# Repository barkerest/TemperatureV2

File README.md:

# TemperatureV2
A POE powered ethernet temperature sensor with two probes.

I wanted to be able to monitor temperatures in various locations
in my server rooms.  Most products on the market were designed
around having a head unit that you plug probes into.  This 
doesn't work for me since the locations I want to monitor have
a fair bit of distance between them.  My solution is a POE 
powered unit with two attached sensors.  I can put them anywhere
without concerning myself with power availability.

## Hardware
The system is based on an Adafruit Feather M0 Basic paired with
a Silicognition PoE FeatherWing and two DS18B20 sensors on leads.

The setup is extremely simple.  The FeatherWing gets attached 
to the M0, including the SDA and SCL pins.  A single 4.7k 
resistor ties pin 5 or 6 to 3v3 and the data lead of both sensors.

This setup costs about $50, and even spending that on each unit
I want to deploy, it still costs less than the commercial
solutions.

## Enclosure
To protect the unit we need an enclosure.  The enclosure needs
to be able to release about 1W of heat from the PoE components.

The enclosure included can easily accomplish that and exposes
the USB port for reprogramming (or external power).  The battery
connector is not exposed in this enclosure.

## Software
Based on some Arduino libraries, the included software manages
the sensors and serves up a very basic webpage.

You may notice this is V2.  V1 was considerably larger based 
on an Arduino.  It produced more heat, and the firmware had to
be altered for each unit to program the MAC address.  Since the
FeatherWing includes a globally unique MAC address, we don't 
need to change the firmware for each unit.

Since this is V2, I wanted to maintain backwards compatibility
with V1.  That's not hard, it just means that the root request
"/" can only return temperatures T1 and T2.  I added a second
endpoint "/v" which returns the MAC address (serial number) and
version of the software in addition to the temperatures.

In production, you'll want to setup DHCP reservations for the
sensors so that they are always where you expect.

## Bugs
None that I know of. However, you cannot power cycle the DS18B20
sensors rapidly.  Because of that, if the unit loses power for
less than a second it may not be able to locate one or both of
the sensors when it boots back up.  In production this shouldn't
happen, but I was able to produce the issue several times during
development by quickly unplugging and plugging back in to reset
the hardware.

## License
Copyright (C) 2021 Beau Barker

Permission is hereby granted, free of charge, to any person
obtaining a copy of this software and associated documentation
files (the "Software"), to deal in the Software without
restriction, including without limitation the rights to use,
copy, modify, merge, publish, distribute, sublicense, and/or
sell copies of the Software, and to permit persons to whom the
Software is furnished to do so, subject to the following
conditions:

The above copyright notice and this permission notice shall be
included in all copies or substantial portions of the Software.

THE SOFTWARE IS PROVIDED "AS IS", WITHOUT WARRANTY OF ANY KIND,
EXPRESS OR IMPLIED, INCLUDING BUT NOT LIMITED TO THE WARRANTIES
OF MERCHANTABILITY, FITNESS FOR A PARTICULAR PURPOSE AND
NONINFRINGEMENT. IN NO EVENT SHALL THE AUTHORS OR COPYRIGHT
HOLDERS BE LIABLE FOR ANY CLAIM, DAMAGES OR OTHER LIABILITY,
WHETHER IN AN ACTION OF CONTRACT, TORT OR OTHERWISE, ARISING
FROM, OUT OF OR IN CONNECTION WITH THE SOFTWARE OR THE USE OR
OTHER DEALINGS IN THE SOFTWARE.

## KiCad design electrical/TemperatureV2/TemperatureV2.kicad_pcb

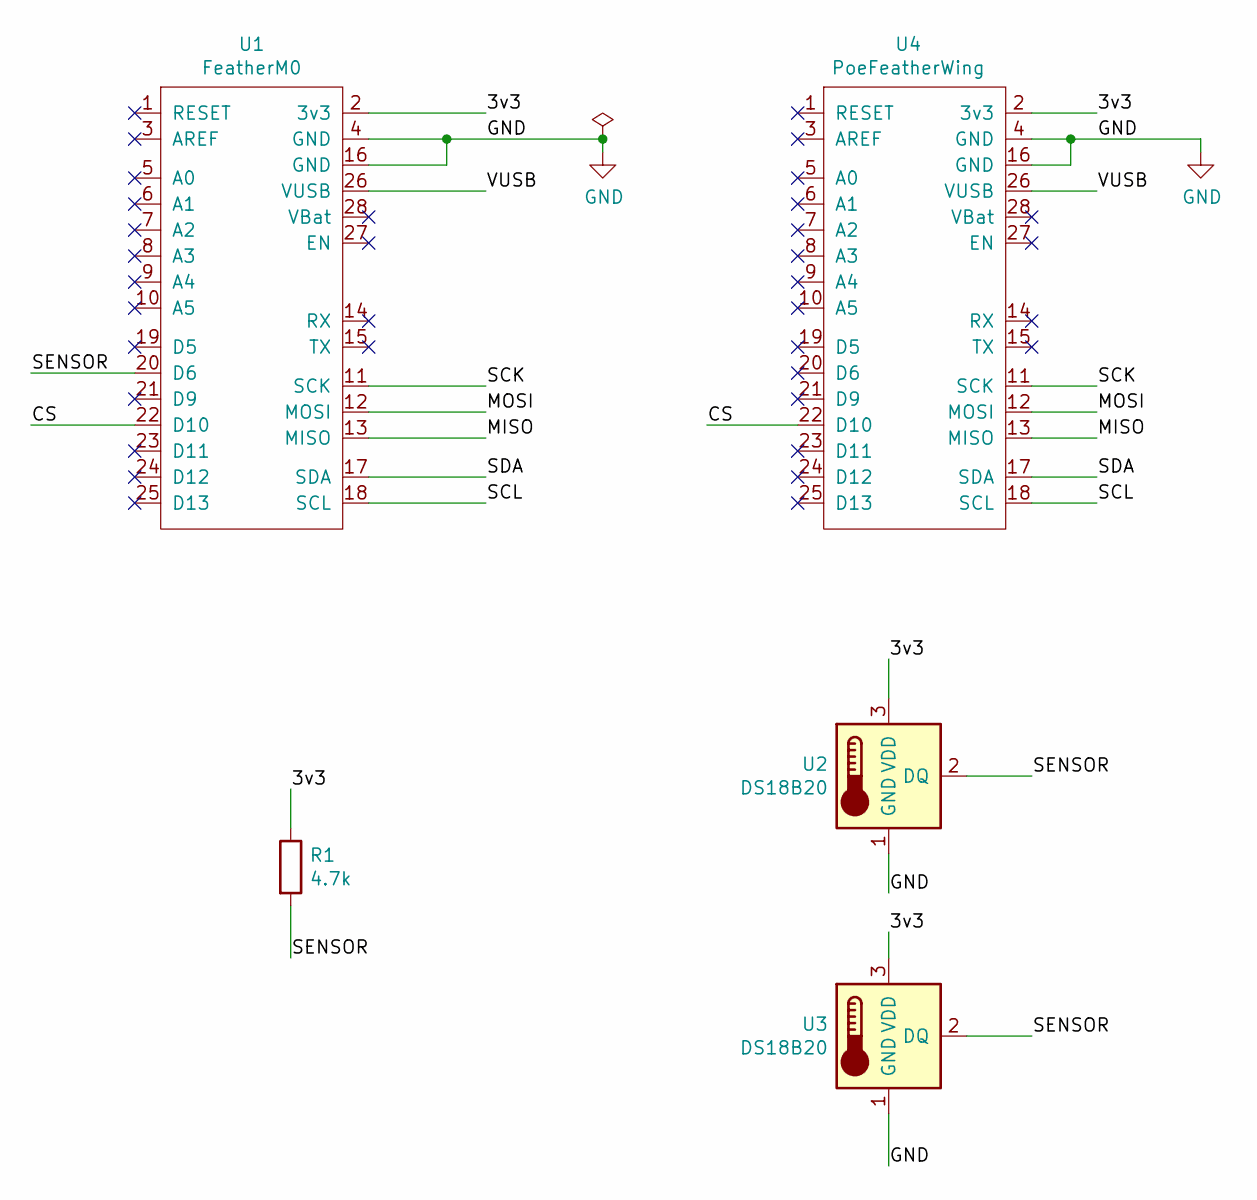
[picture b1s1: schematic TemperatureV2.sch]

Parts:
R1: 4.7k; R_Axial_DIN0207_L6.3mm_D2.5mm_P7.62mm_Horizontal
U1: FeatherM0
U2, U3: DS18B20; TO-92_Inline
U4: PoeFeatherWing; EthernetWing

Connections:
/3v3: R1.1, U1.2 (3v3), U2.3 (VDD), U3.3 (VDD), U4.2 (3v3)
/CS: U1.22 (D10), U4.22 (D10)
/MISO: U1.13 (MISO), U4.13 (MISO)
/MOSI: U1.12 (MOSI), U4.12 (MOSI)
/SCK: U1.11 (SCK), U4.11 (SCK)
/SCL: U1.18 (SCL), U4.18 (SCL)
/SDA: U1.17 (SDA), U4.17 (SDA)
/SENSOR: R1.2, U1.20 (D6), U2.2 (DQ), U3.2 (DQ)
/VUSB: U1.26 (VUSB), U4.26 (VUSB)
GND: U1.4 (GND), U1.16 (GND), U2.1 (GND), U3.1 (GND), U4.4 (GND), U4.16 (GND)

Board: 2 copper layers, 5 parts (0 on the bottom side), 10 nets, no tracks yet.

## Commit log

2021-04-24 Initialize repo.
2021-04-24 Add reinit code to sensors and update enclosure.
2021-04-26 Rename and add ability to print two boxes.
